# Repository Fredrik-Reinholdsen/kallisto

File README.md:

# Kallisto

A custom split keyboard, with custom electronics and firmware.

The hardware is based around a variant of the _Raspberry Pi Pico_ board, and the _RP2040_ microcontroller.
The keyboard features:

- 42 Kailh 1350 mechanical keyswitches (21 per half), 4 extra buttons and one rotary encoder.
- Fully programmable key-map were any key can be mapped to any key/media function.
- Key-map Layers
- Custom RGB lighting with adjustable brightness
- Onboard flash memory that hold the key-map.

All electronics were designed using KiCad, and all firmware is written in Rust.

## Key Mapping
Any physical key on the keyboard may be mapped to any key, with or without an additional modifier.
Buttons have a few different press modes, similar to the *QMK* firmware, that you can map separatley to different keys.

The different key press types/events are:
- Press
- Held Press
- Double Press

### Held Press
A held press is when a button is pressed and held, for a set ammount of time (0.5s by default).
If a button has a held press mapping is pressed and then released before the held-time window,
then the regular _Press_ mapping while fire upon the release, not the press.
If another button is pressed before the end of the held-time window, then the held press mapping while fire immediatley,
and the other pressed button will fire right after.
If a button with a held press mapping is pressed and held for more than the held-time window, and no other button is pressed in between,
then the held press key mapping will fire.

## Software Design
The right half of the keyboard connected to the host PC acts as the master, and the the left half as the slave.
Compiling the embedded software will generate two separate binaries, one for the master half, and one for the slave.

The slave software is very light-weight and is basically only reading the button matrix, and communicating the current
button states to the master half vi I2C. This means that the slave, once flashed, should rarely need to be re-programmed since the
vast majority of the more complicated application code is running on the master half.

Below is a figure showing the overall architecture of the software that is running on each half of the keyboard.
```mermaid
flowchart RL
    subgraph Master
        direction BT
        BMR[Button Matrix] --> KEGR(Key Event Generator)
        KEGR -->|Key Event| BEG(Button Event Generator)
        BEG -->|Button Event| BEM(Button Event Mapper)
        BEM -->|USB HID Event| USB(USB HID)
    end

    subgraph Slave
        direction BT
        BML[Button Matrix] --> KEGL(Key Event Generator)
    end

    Slave -->|Key Events| Master
```
### Key Event Generator
The `Key Event Generator` reads the current states of all keyboard buttons from the button matrix driver, and generates key press events.
Either key-down or key-up events, based on the current, and the previous button states. Key press events and IDs are constantly
streamed from the slave to the master half via I2C.
These key events from both halves are then queued on the master, along with a unique button ID for which physical button that triggered the event.

### Button Event Generator
The `Button Event Generator` then reads the incoming key press events, and correspoding button IDs from the key-event queue.
This information is then used to generate `Button Events`. The different kinds are:
- Single Press
- Held Press
- Double Press

A held press is triggered if a button is pressed and held for more than 0.3 seconds, and a double press is generated
if a button is pressed twice within 0.3 seconds (these times are tweakable).

The button events along with the ID of which physical button produced the event are then passed `Button Event Mapper`

### Button Event Mapper
The `Button Event Mapper` then maps the incoming button IDs and button event types to a key-press to be sent to the host PC via USB.
For example, single pressing the z-key might map to `z`, but pressing and hold it might map to `Ctrl`. This mapping for each physical button,
and button event type is fully customizable.

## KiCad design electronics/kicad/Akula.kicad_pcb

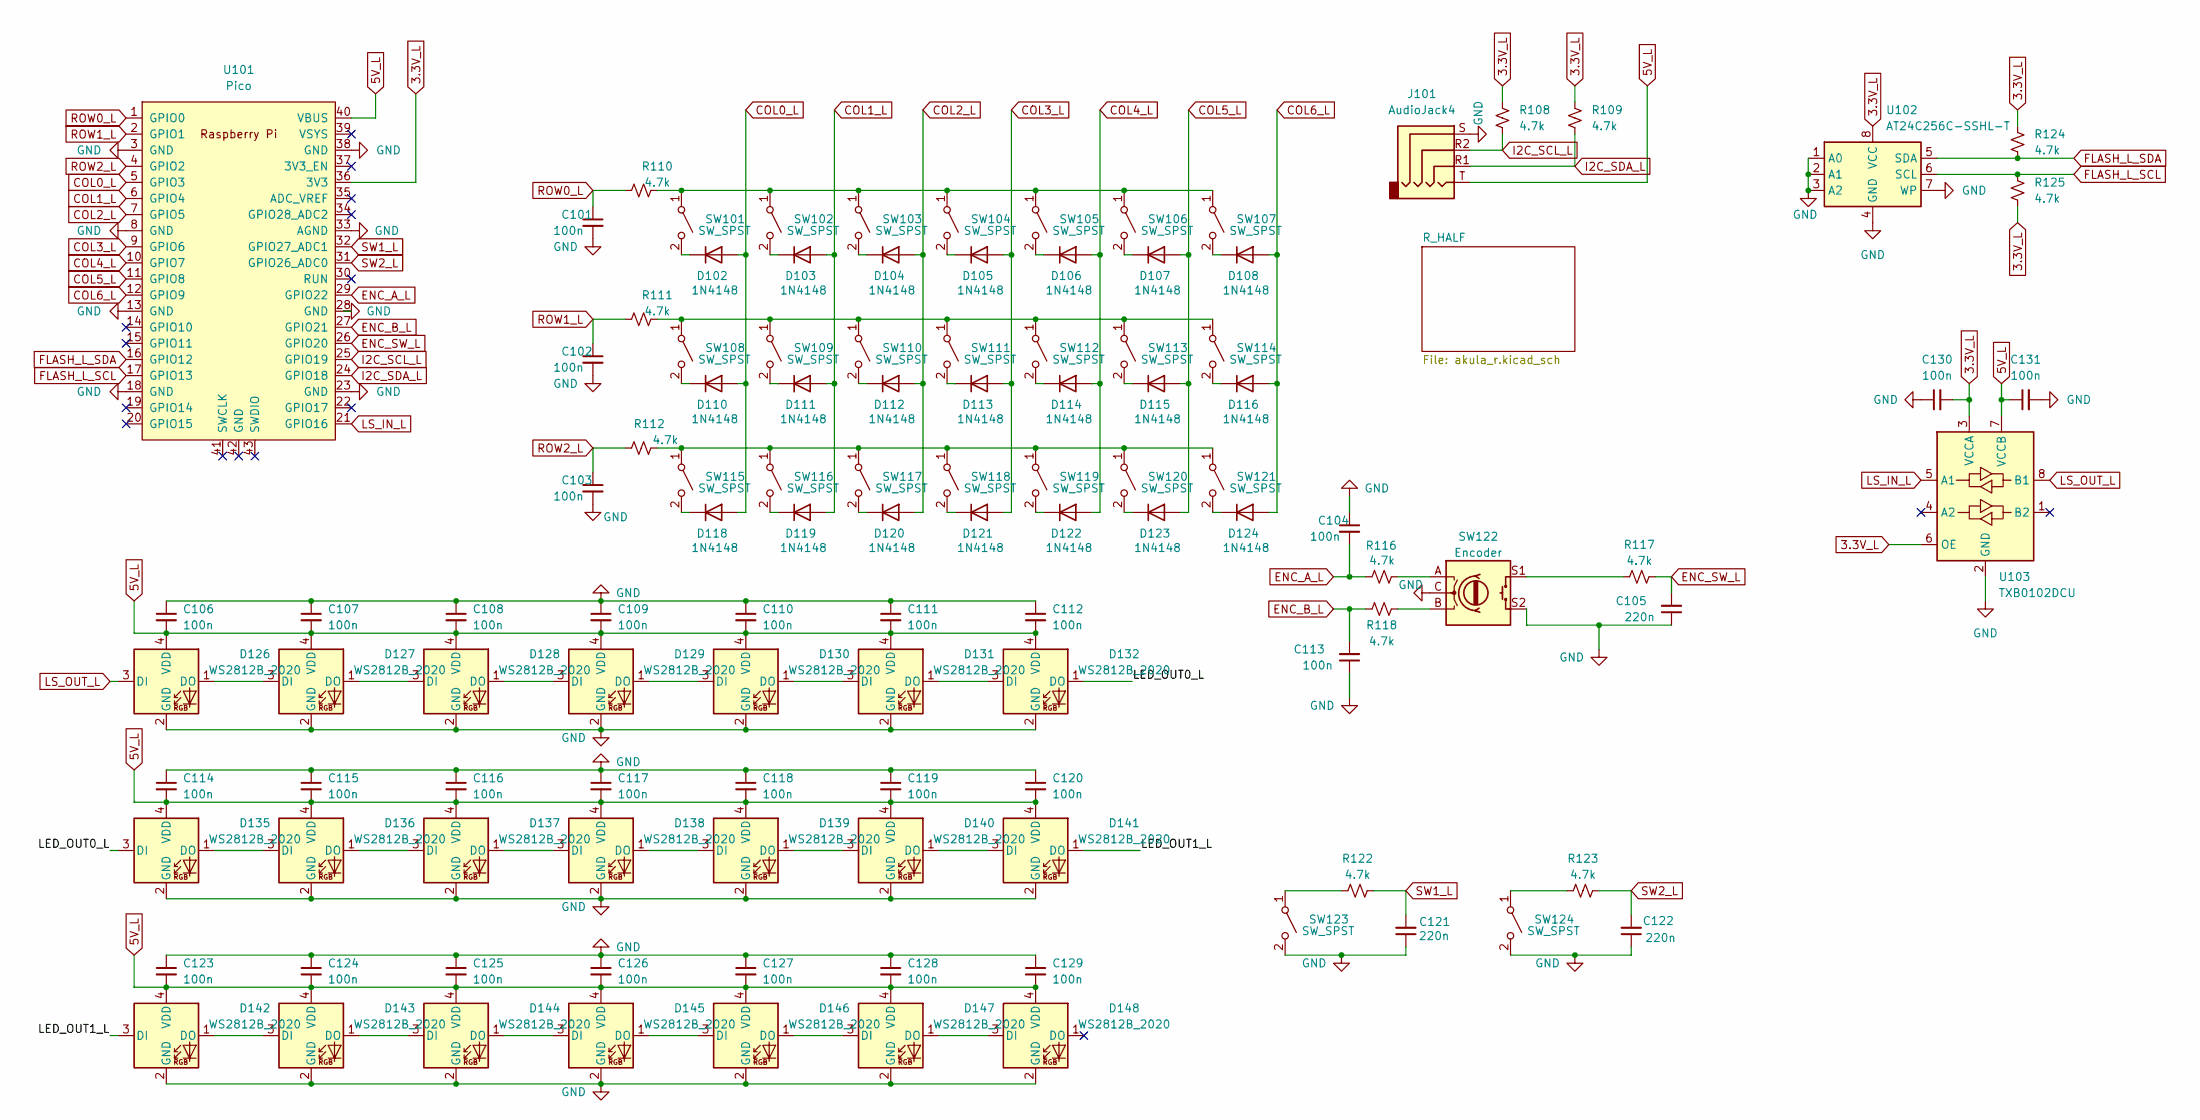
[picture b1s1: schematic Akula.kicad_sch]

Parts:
C101, C102, C103, C104, C106, C107, C108, C109, C110, C111, C112, C113, C114, C115, C116, C117, C118, C119, C120, C123, C124, C125, C126, C127, C128, C129, C130, C131: 100n; C_0402_1005Metric; JLCPCB Part # C1525
C105, C121, C122: 220n; C_0402_1005Metric; JLCPCB Part # C16772
D102, D103, D104, D105, D106, D107, D108, D110, D111, D112, D113, D114, D115, D116, D118, D119, D120, D121, D122, D123, D124: 1N4148; D_SOD-323; JLCPCB Part # C2128
D126, D127, D128, D129, D130, D131, D132, D135, D136, D137, D138, D139, D140, D141, D142, D143, D144, D145, D146, D147, D148: WS2812B_2020; LED_WS2812B-2020_PLCC4_2.0x2.0mm; JLCPCB Part # C965555
J101: AudioJack4; Jack_3.5mm_PJ320D_Horizontal; JLCPCB Part # C431535
R108, R109, R110, R111, R112, R116, R117, R118, R122, R123, R124, R125: 4.7k; R_0402_1005Metric; JLCPCB Part # C25900
SW101, SW102, SW103, SW104, SW105, SW106, SW107, SW108, SW109, SW110, SW111, SW112, SW113, SW114, SW115, SW116, SW117, SW118, SW119, SW120, SW121: SW_SPST; SW_PG1350
SW122: Encoder; RotaryEncoder_Alps_EC11E-Switch_Vertical_H20mm_CircularMoun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; JLCPCB Part # C470753
SW123, SW124: SW_SPST; SW_PUSH-12mm; JLCPCB Part # C93155
U101: Pico; RPi_Pico_SMD_TH
U102: AT24C256C-SSHL-T; SOIC-8_3.9x4.9mm_P1.27mm; JLCPCB Part # C6482
U103: TXB0102DCU; VSSOP-8_2.4x2.1mm_P0.5mm; JLCPCB Part # C2677366

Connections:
3.3V_L: C130.2, R108.2, R109.2, R124.2, R125.2, U101.36 (3V3), U102.8 (VCC), U103.3 (VCCA), U103.6 (OE)
5V_L: C106.2, C107.2, C108.2, C109.2, C110.2, C111.2, C112.2, C114.2, C115.2, C116.2, C117.2, C118.2, C119.2, C120.2, C123.2, C124.2, C125.2, C126.2, C127.2, C128.2, C129.2, C131.1, D126.4 (VDD), D127.4 (VDD), D128.4 (VDD), D129.4 (VDD), D130.4 (VDD), D131.4 (VDD), D132.4 (VDD), D135.4 (VDD), D136.4 (VDD), D137.4 (VDD), D138.4 (VDD), D139.4 (VDD), D140.4 (VDD), D141.4 (VDD), D142.4 (VDD), D143.4 (VDD), D144.4 (VDD), D145.4 (VDD), D146.4 (VDD), D147.4 (VDD), D148.4 (VDD), J101.T, U101.40 (VBUS), U103.7 (VCCB)
/LED_OUT0_L: D132.1 (DO), D135.3 (DI)
/LED_OUT1_L: D141.1 (DO), D142.3 (DI)
COL0_L: D102.2 (A), D110.2 (A), D118.2 (A), U101.5 (GPIO3)
COL1_L: D103.2 (A), D111.2 (A), D119.2 (A), U101.6 (GPIO4)
COL2_L: D104.2 (A), D112.2 (A), D120.2 (A), U101.7 (GPIO5)
COL3_L: D105.2 (A), D113.2 (A), D121.2 (A), U101.9 (GPIO6)
COL4_L: D106.2 (A), D114.2 (A), D122.2 (A), U101.10 (GPIO7)
COL5_L: D107.2 (A), D115.2 (A), D123.2 (A), U101.11 (GPIO8)
COL6_L: D108.2 (A), D116.2 (A), D124.2 (A), U101.12 (GPIO9)
ENC_A_L: C104.2, R116.2, U101.29 (GPIO22)
ENC_B_L: C113.2, R118.2, U101.27 (GPIO21)
ENC_SW_L: C105.2, R117.1, U101.26 (GPIO20)
FLASH_L_SCL: R125.1, U101.17 (GPIO13), U102.6 (SCL)
FLASH_L_SDA: R124.1, U101.16 (GPIO12), U102.5 (SDA)
GND: C101.2, C102.2, C103.2, C104.1, C105.1, C106.1, C107.1, C108.1, C109.1, C110.1, C111.1, C112.1, C113.1, C114.1, C115.1, C116.1, C117.1, C118.1, C119.1, C120.1, C121.1, C122.1, C123.1, C124.1, C125.1, C126.1, C127.1, C128.1, C129.1, C130.1, C131.2, D126.2 (GND), D127.2 (GND), D128.2 (GND), D129.2 (GND), D130.2 (GND), D131.2 (GND), D132.2 (GND), D135.2 (GND), D136.2 (GND), D137.2 (GND), D138.2 (GND), D139.2 (GND), D140.2 (GND), D141.2 (GND), D142.2 (GND), D143.2 (GND), D144.2 (GND), D145.2 (GND), D146.2 (GND), D147.2 (GND), D148.2 (GND), J101.S, SW122.C, SW122.S2, SW123.2 (B), SW124.2 (B), U101.3 (GND), U101.8 (GND), U101.13 (GND), U101.18 (GND), U101.23 (GND), U101.28 (GND), U101.33 (AGND), U101.38 (GND), U102.1 (A0), U102.2 (A1), U102.3 (A2), U102.4 (GND), U102.7 (WP), U103.2 (GND)
I2C_SCL_L: J101.R2, R108.1, U101.25 (GPIO19)
I2C_SDA_L: J101.R1, R109.1, U101.24 (GPIO18)
LS_IN_L: U101.21 (GPIO16), U103.5 (A1)
LS_OUT_L: D126.3 (DI), U103.8 (B1)
unnamed: D102.1 (K), SW101.2 (B)
unnamed: D103.1 (K), SW102.2 (B)
unnamed: D104.1 (K), SW103.2 (B)
unnamed: D105.1 (K), SW104.2 (B)
unnamed: D106.1 (K), SW105.2 (B)
unnamed: D107.1 (K), SW106.2 (B)
unnamed: D108.1 (K), SW107.2 (B)
unnamed: D110.1 (K), SW108.2 (B)
unnamed: D111.1 (K), SW109.2 (B)
unnamed: D112.1 (K), SW110.2 (B)
unnamed: D113.1 (K), SW111.2 (B)
unnamed: D114.1 (K), SW112.2 (B)
unnamed: D115.1 (K), SW113.2 (B)
unnamed: D116.1 (K), SW114.2 (B)
unnamed: D118.1 (K), SW115.2 (B)
unnamed: D119.1 (K), SW116.2 (B)
unnamed: D120.1 (K), SW117.2 (B)
unnamed: D121.1 (K), SW118.2 (B)
unnamed: D122.1 (K), SW119.2 (B)
unnamed: D123.1 (K), SW120.2 (B)
unnamed: D124.1 (K), SW121.2 (B)
unnamed: D126.1 (DO), D127.3 (DI)
unnamed: D127.1 (DO), D128.3 (DI)
unnamed: D128.1 (DO), D129.3 (DI)
unnamed: D129.1 (DO), D130.3 (DI)
unnamed: D130.1 (DO), D131.3 (DI)
unnamed: D131.1 (DO), D132.3 (DI)
unnamed: D135.1 (DO), D136.3 (DI)
unnamed: D136.1 (DO), D137.3 (DI)
unnamed: D137.1 (DO), D138.3 (DI)
unnamed: D138.1 (DO), D139.3 (DI)
unnamed: D139.1 (DO), D140.3 (DI)
unnamed: D140.1 (DO), D141.3 (DI)
unnamed: D142.1 (DO), D143.3 (DI)
unnamed: D143.1 (DO), D144.3 (DI)
unnamed: D144.1 (DO), D145.3 (DI)
unnamed: D145.1 (DO), D146.3 (DI)
unnamed: D146.1 (DO), D147.3 (DI)
unnamed: D147.1 (DO), D148.3 (DI)
unnamed: R116.1, SW122.A
unnamed: R117.2, SW122.S1
unnamed: R118.1, SW122.B
unnamed: R110.1, SW101.1 (A), SW102.1 (A), SW103.1 (A), SW104.1 (A), SW105.1 (A), SW106.1 (A), SW107.1 (A)
unnamed: R111.1, SW108.1 (A), SW109.1 (A), SW110.1 (A), SW111.1 (A), SW112.1 (A), SW113.1 (A), SW114.1 (A)
unnamed: R112.1, SW115.1 (A), SW116.1 (A), SW117.1 (A), SW118.1 (A), SW119.1 (A), SW120.1 (A), SW121.1 (A)
unnamed: R122.2, SW123.1 (A)
unnamed: R123.2, SW124.1 (A)
ROW0_L: C101.1, R110.2, U101.1 (GPIO0)
ROW1_L: C102.1, R111.2, U101.2 (GPIO1)
ROW2_L: C103.1, R112.2, U101.4 (GPIO2)
SW1_L: C121.2, R122.1, U101.32 (GPIO27_ADC1)
SW2_L: C122.2, R123.1, U101.31 (GPIO26_ADC0)

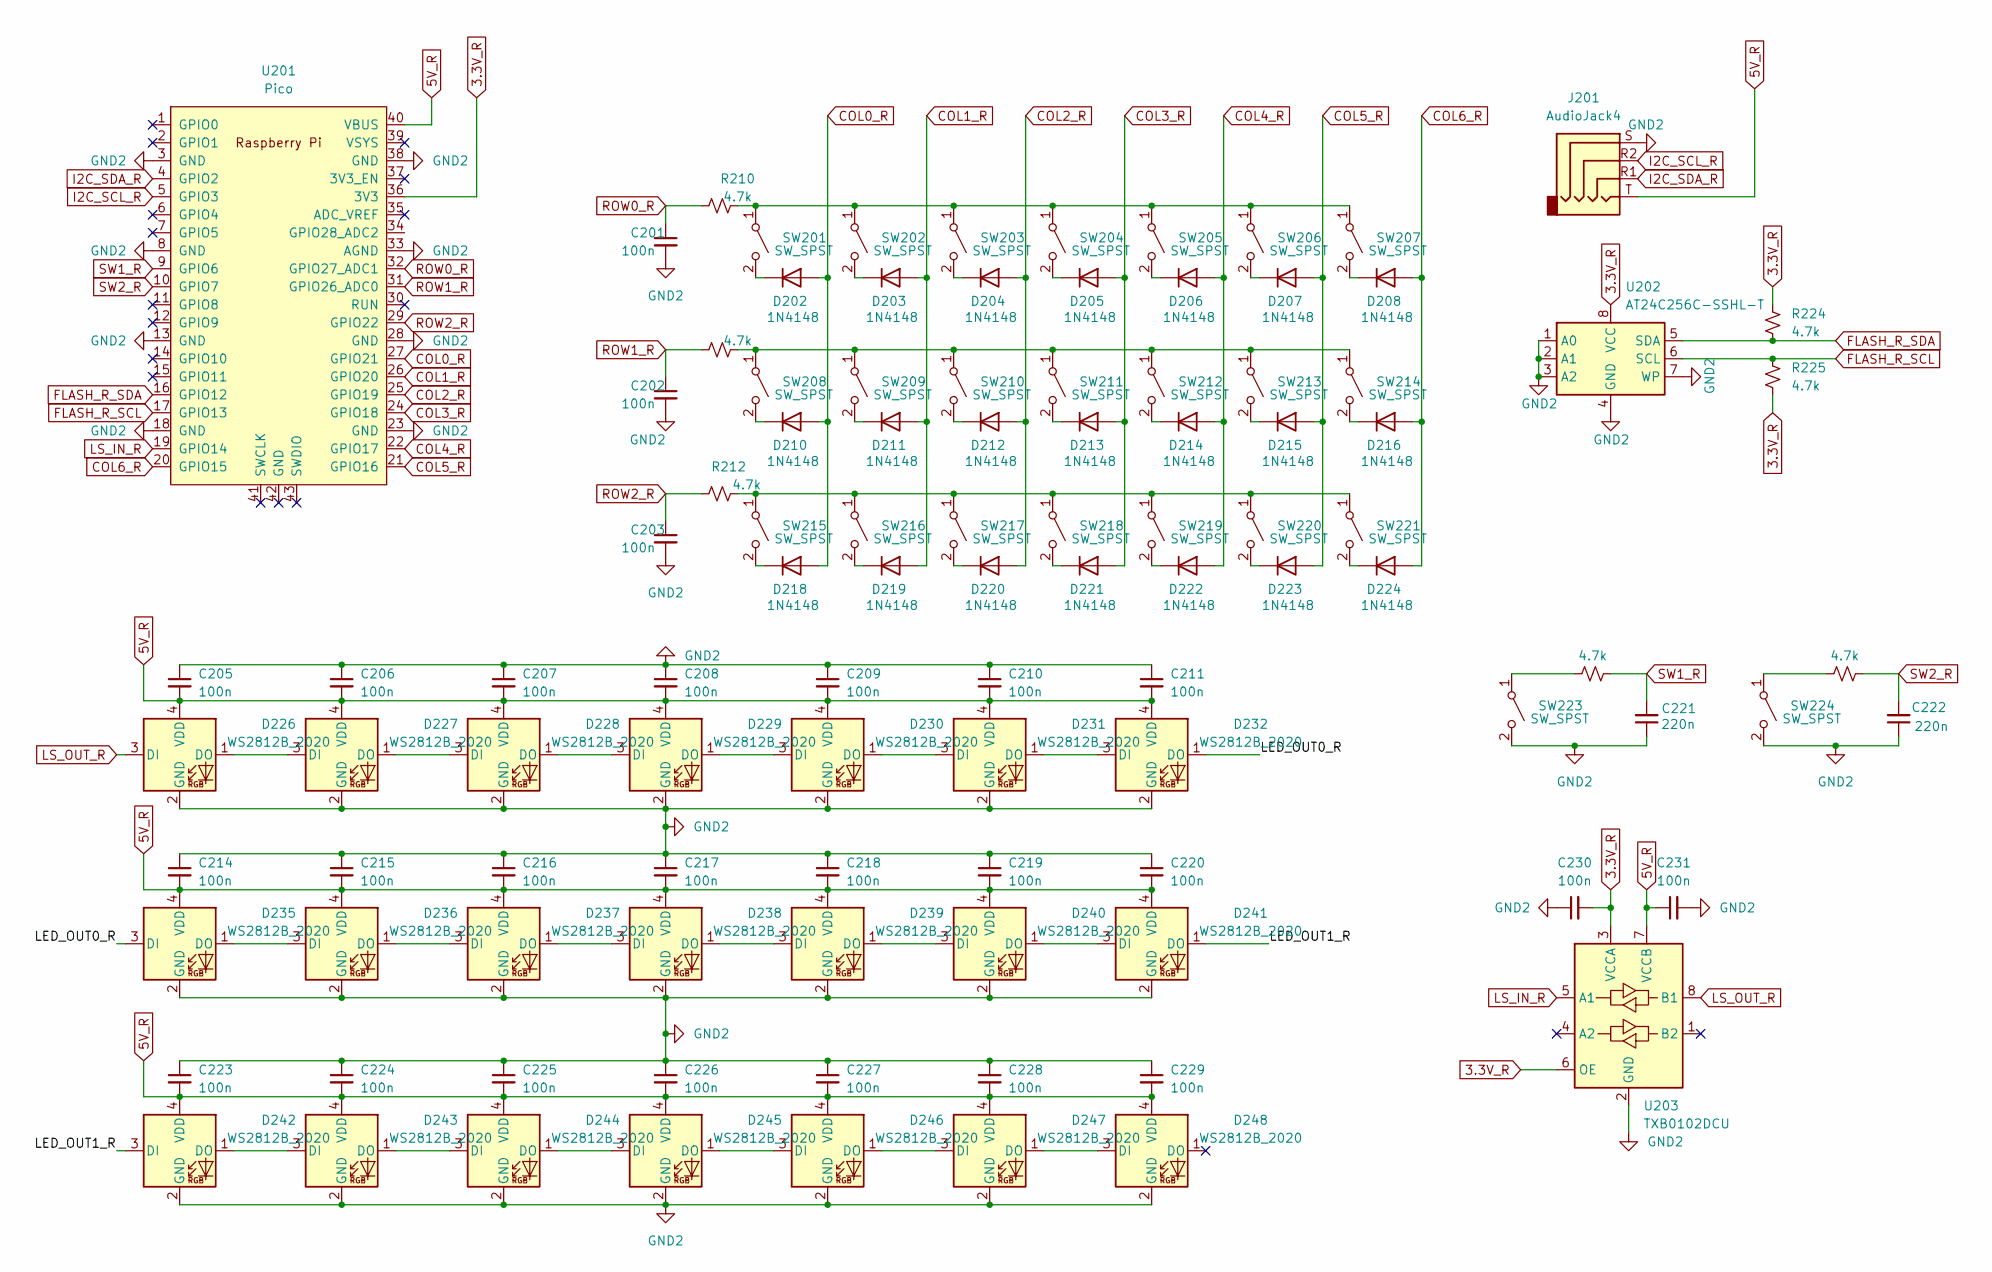
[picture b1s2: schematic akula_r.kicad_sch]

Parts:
C201, C202, C203, C205, C206, C207, C208, C209, C210, C211, C214, C215, C216, C217, C218, C219, C220, C223, C224, C225, C226, C227, C228, C229, C230, C231: 100n; C_0402_1005Metric; JLCPCB Part # C1525
C221, C222: 220n; C_0402_1005Metric; JLCPCB Part # C16772
D202, D203, D204, D205, D206, D207, D208, D210, D211, D212, D213, D214, D215, D216, D218, D219, D220, D221, D222, D223, D224: 1N4148; D_SOD-323; JLCPCB Part # C2128
D226, D227, D228, D229, D230, D231, D232, D235, D236, D237, D238, D239, D240, D241, D242, D243, D244, D245, D246, D247, D248: WS2812B_2020; LED_WS2812B-2020_PLCC4_2.0x2.0mm; JLCPCB Part # C965555
J201: AudioJack4; Jack_3.5mm_PJ320D_Horizontal; JLCPCB Part # C431535
R210, R211, R212, R222, R223, R224, R225: 4.7k; R_0402_1005Metric; JLCPCB Part # C25900
SW201, SW202, SW203, SW204, SW205, SW206, SW207, SW208, SW209, SW210, SW211, SW212, SW213, SW214, SW215, SW216, SW217, SW218, SW219, SW220, SW221: SW_SPST; SW_PG1350
SW223, SW224: SW_SPST; SW_PUSH-12mm; JLCPCB Part # C93155
U201: Pico; RPi_Pico_SMD_TH
U202: AT24C256C-SSHL-T; SOIC-8_3.9x4.9mm_P1.27mm; JLCPCB Part # C6482
U203: TXB0102DCU; VSSOP-8_2.4x2.1mm_P0.5mm; JLCPCB Part # C2677366

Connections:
3.3V_R: C230.2, R224.2, R225.2, U201.36 (3V3), U202.8 (VCC), U203.3 (VCCA), U203.6 (OE)
5V_R: C205.2, C206.2, C207.2, C208.2, C209.2, C210.2, C211.2, C214.2, C215.2, C216.2, C217.2, C218.2, C219.2, C220.2, C223.2, C224.2, C225.2, C226.2, C227.2, C228.2, C229.2, C231.1, D226.4 (VDD), D227.4 (VDD), D228.4 (VDD), D229.4 (VDD), D230.4 (VDD), D231.4 (VDD), D232.4 (VDD), D235.4 (VDD), D236.4 (VDD), D237.4 (VDD), D238.4 (VDD), D239.4 (VDD), D240.4 (VDD), D241.4 (VDD), D242.4 (VDD), D243.4 (VDD), D244.4 (VDD), D245.4 (VDD), D246.4 (VDD), D247.4 (VDD), D248.4 (VDD), J201.T, U201.40 (VBUS), U203.7 (VCCB)
/R_HALF/LED_OUT0_R: D232.1 (DO), D235.3 (DI)
/R_HALF/LED_OUT1_R: D241.1 (DO), D242.3 (DI)
COL0_R: D202.2 (A), D210.2 (A), D218.2 (A), U201.27 (GPIO21)
COL1_R: D203.2 (A), D211.2 (A), D219.2 (A), U201.26 (GPIO20)
COL2_R: D204.2 (A), D212.2 (A), D220.2 (A), U201.25 (GPIO19)
COL3_R: D205.2 (A), D213.2 (A), D221.2 (A), U201.24 (GPIO18)
COL4_R: D206.2 (A), D214.2 (A), D222.2 (A), U201.22 (GPIO17)
COL5_R: D207.2 (A), D215.2 (A), D223.2 (A), U201.21 (GPIO16)
COL6_R: D208.2 (A), D216.2 (A), D224.2 (A), U201.20 (GPIO15)
FLASH_R_SCL: R225.1, U201.17 (GPIO13), U202.6 (SCL)
FLASH_R_SDA: R224.1, U201.16 (GPIO12), U202.5 (SDA)
GND2: C201.2, C202.2, C203.2, C205.1, C206.1, C207.1, C208.1, C209.1, C210.1, C211.1, C214.1, C215.1, C216.1, C217.1, C218.1, C219.1, C220.1, C221.1, C222.1, C223.1, C224.1, C225.1, C226.1, C227.1, C228.1, C229.1, C230.1, C231.2, D226.2 (GND), D227.2 (GND), D228.2 (GND), D229.2 (GND), D230.2 (GND), D231.2 (GND), D232.2 (GND), D235.2 (GND), D236.2 (GND), D237.2 (GND), D238.2 (GND), D239.2 (GND), D240.2 (GND), D241.2 (GND), D242.2 (GND), D243.2 (GND), D244.2 (GND), D245.2 (GND), D246.2 (GND), D247.2 (GND), D248.2 (GND), J201.S, SW223.2 (B), SW224.2 (B), U201.3 (GND), U201.8 (GND), U201.13 (GND), U201.18 (GND), U201.23 (GND), U201.28 (GND), U201.33 (AGND), U201.38 (GND), U202.1 (A0), U202.2 (A1), U202.3 (A2), U202.4 (GND), U202.7 (WP), U203.2 (GND)
I2C_SCL_R: J201.R2, U201.5 (GPIO3)
I2C_SDA_R: J201.R1, U201.4 (GPIO2)
LS_IN_R: U201.19 (GPIO14), U203.5 (A1)
LS_OUT_R: D226.3 (DI), U203.8 (B1)
unnamed: D202.1 (K), SW201.2 (B)
unnamed: D203.1 (K), SW202.2 (B)
unnamed: D204.1 (K), SW203.2 (B)
unnamed: D205.1 (K), SW204.2 (B)
unnamed: D206.1 (K), SW205.2 (B)
unnamed: D207.1 (K), SW206.2 (B)
unnamed: D208.1 (K), SW207.2 (B)
unnamed: D210.1 (K), SW208.2 (B)
unnamed: D211.1 (K), SW209.2 (B)
unnamed: D212.1 (K), SW210.2 (B)
unnamed: D213.1 (K), SW211.2 (B)
unnamed: D214.1 (K), SW212.2 (B)
unnamed: D215.1 (K), SW213.2 (B)
unnamed: D216.1 (K), SW214.2 (B)
unnamed: D218.1 (K), SW215.2 (B)
unnamed: D219.1 (K), SW216.2 (B)
unnamed: D220.1 (K), SW217.2 (B)
unnamed: D221.1 (K), SW218.2 (B)
unnamed: D222.1 (K), SW219.2 (B)
unnamed: D223.1 (K), SW220.2 (B)
unnamed: D224.1 (K), SW221.2 (B)
unnamed: D226.1 (DO), D227.3 (DI)
unnamed: D227.1 (DO), D228.3 (DI)
unnamed: D228.1 (DO), D229.3 (DI)
unnamed: D229.1 (DO), D230.3 (DI)
unnamed: D230.1 (DO), D231.3 (DI)
unnamed: D231.1 (DO), D232.3 (DI)
unnamed: D235.1 (DO), D236.3 (DI)
unnamed: D236.1 (DO), D237.3 (DI)
unnamed: D237.1 (DO), D238.3 (DI)
unnamed: D238.1 (DO), D239.3 (DI)
unnamed: D239.1 (DO), D240.3 (DI)
unnamed: D240.1 (DO), D241.3 (DI)
unnamed: D242.1 (DO), D243.3 (DI)
unnamed: D243.1 (DO), D244.3 (DI)
unnamed: D244.1 (DO), D245.3 (DI)
unnamed: D245.1 (DO), D246.3 (DI)
unnamed: D246.1 (DO), D247.3 (DI)
unnamed: D247.1 (DO), D248.3 (DI)
unnamed: R210.1, SW201.1 (A), SW202.1 (A), SW203.1 (A), SW204.1 (A), SW205.1 (A), SW206.1 (A), SW207.1 (A)
unnamed: R211.1, SW208.1 (A), SW209.1 (A), SW210.1 (A), SW211.1 (A), SW212.1 (A), SW213.1 (A), SW214.1 (A)
unnamed: R212.1, SW215.1 (A), SW216.1 (A), SW217.1 (A), SW218.1 (A), SW219.1 (A), SW220.1 (A), SW221.1 (A)
unnamed: R222.2, SW223.1 (A)
unnamed: R223.2, SW224.1 (A)
ROW0_R: C201.1, R210.2, U201.32 (GPIO27_ADC1)
ROW1_R: C202.1, R211.2, U201.31 (GPIO26_ADC0)
ROW2_R: C203.1, R212.2, U201.29 (GPIO22)
SW1_R: C221.2, R222.1, U201.9 (GPIO6)
SW2_R: C222.2, R223.1, U201.10 (GPIO7)

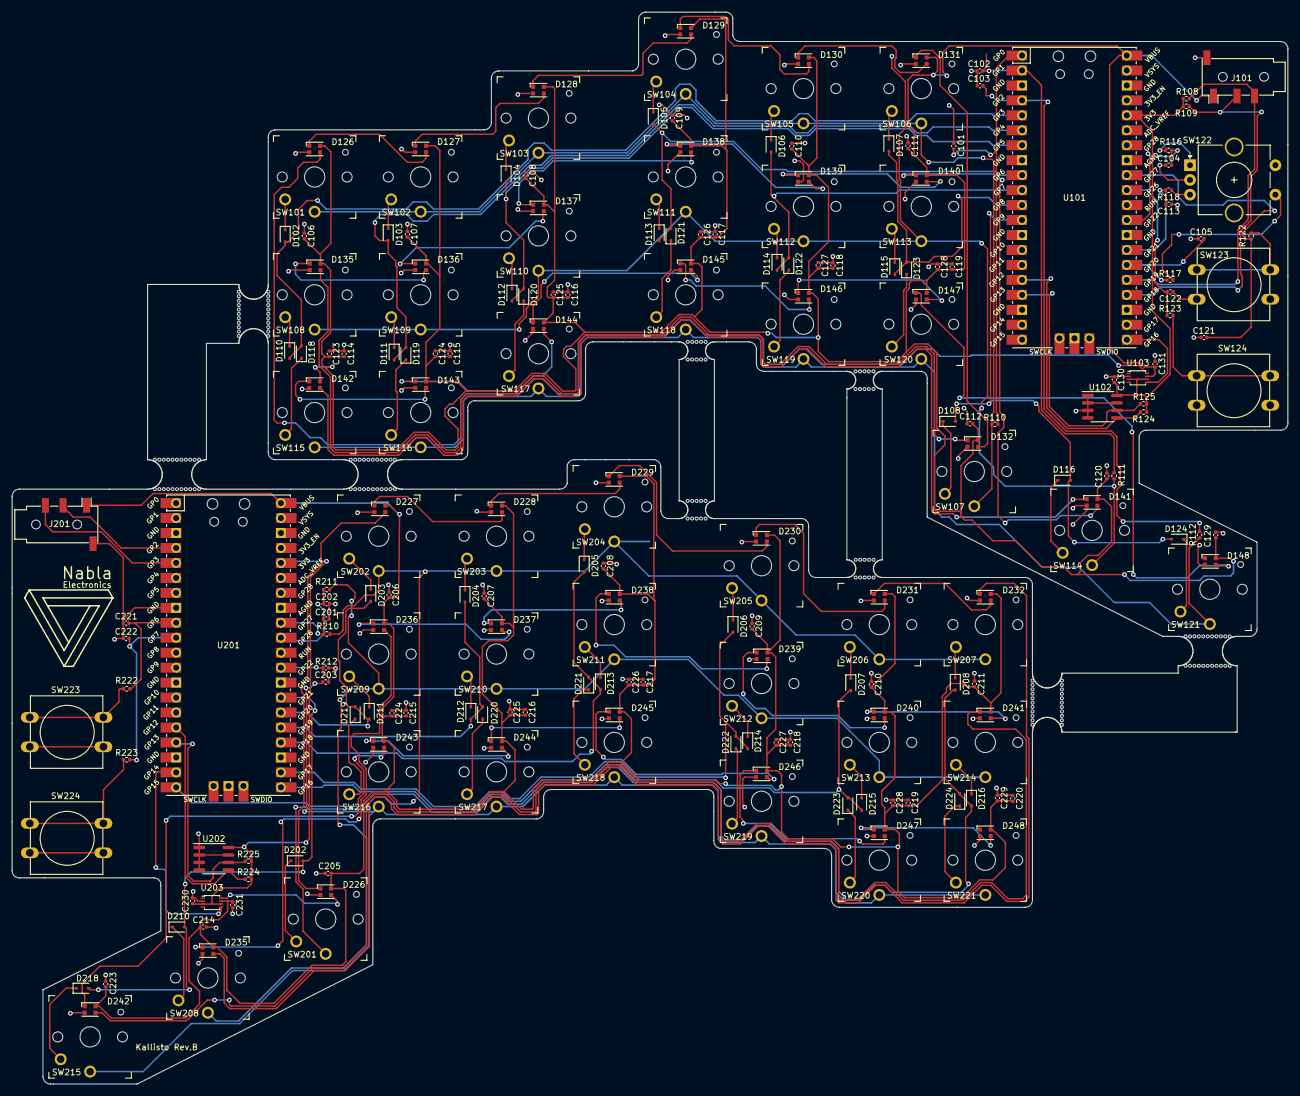
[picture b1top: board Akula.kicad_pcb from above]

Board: 2 copper layers, 216.6 x 182.0 mm, 226 parts (0 on the bottom side), 140 nets.

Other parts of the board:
mouse-bite-3mm-slot, mouse-bite-3mm-slot#2, mouse-bite-3mm-slot#3, mouse-bite-3mm-slot#4: VAL**; mouse-bite-3mm-slot
mouse-bite-5mm-slot, mouse-bite-5mm-slot#2, mouse-bite-5mm-slot#3, mouse-bite-5mm-slot#4, mouse-bite-5mm-slot#5: VAL**; mouse-bite-5mm-slot

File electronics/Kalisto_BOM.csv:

"Comment","Designator","Footprint","LCSC Part #"
"100n","C101,C102,C103,C104,C106,C107,C108,C109,C110,C111,C112,C113,C114,C115,C116,C117,C118,C119,C120,C123,C124,C125,C126,C127,C128,C129,C130,C131,C201,C202,C203,C205,C206,C207,C208,C209,C210,C211,C214,C215,C216,C217,C218,C219,C220,C223,C224,C225,C226,C227,C228,C229,C230,C231","C_0402_1005Metric","C1525"
"220n","C105,C121,C122,C221,C222","C_0402_1005Metric","C16772"
"1N4148","D102,D103,D104,D105,D106,D107,D108,D110,D111,D112,D113,D114,D115,D116,D118,D119,D120,D121,D122,D123,D124,D202,D203,D204,D205,D206,D207,D208,D210,D211,D212,D213,D214,D215,D216,D218,D219,D220,D221,D222,D223,D224","D_SOD-323","C2128"
"WS2812B_2020","D126,D127,D128,D129,D130,D131,D132,D135,D136,D137,D138,D139,D140,D141,D142,D143,D144,D145,D146,D147,D148,D226,D227,D228,D229,D230,D231,D232,D235,D236,D237,D238,D239,D240,D241,D242,D243,D244,D245,D246,D247,D248","LED_WS2812B-2020_PLCC4_2.0x2.0mm","C965555"
"AudioJack4","J101,J201","Jack_3.5mm_PJ320D_Horizontal","C431535"
"4.7k","R108,R109,R110,R111,R112,R116,R117,R118,R122,R123,R124,R125,R210,R211,R212,R222,R223,R224,R225","R_0402_1005Metric","C25900"
"Encoder","SW122","RotaryEncoder_Alps_EC11E-Switch_Vertical_H20mm_CircularMountingHoles","C470753"
"SW_SPST","SW123,SW124,SW223,SW224","SW_PUSH-12mm","C93155"
"AT24C256C-SSHL-T","U102,U202","SOIC-8_3.9x4.9mm_P1.27mm","C6482"
"TXB0102DCU","U103,U203","VSSOP-8_2.4x2.1mm_P0.5mm","C2677366"

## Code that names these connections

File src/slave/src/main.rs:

#![no_std]
#![no_main]

// The macro for our start-up function
use rp_pico::entry;

// Ensure we halt the program on panic (if we don't mention this crate it won't
// be linked)
use panic_halt as _;

// Pull in any important traits
use rp_pico::hal::prelude::*;

// A shorter alias for the Peripheral Access Crate, which provides low-level
// register access
use rp_pico::hal::{self, pac};

// Import the Timer for Ws2812:
use rp_pico::hal::timer::Timer;
use hal::i2c::I2C;
use hal::i2c::peripheral::I2CEvent;

// A shorter alias for the Hardware Abstraction Layer, which provides
// higher-level drivers.
use kallisto_components::keyboard::key_matrix::KeyMatrix;
use embedded_hal::digital::v2::{InputPin, OutputPin};
use embedded_hal::timer::CountDown;
use heapless::{String, spsc::Queue};
use usb_device::class_prelude::*;
use fugit::ExtU32;

use usb_device::{class_prelude::*, prelude::*};
use usbd_serial::SerialPort;
use core::fmt::Write;

use hal::pio::PIOExt;
use smart_leds::{brightness, SmartLedsWrite, RGB8};
use ws2812_pio::Ws2812;

// Currently 3 consecutive LEDs are driven by this example
// to keep the power draw compatible with USB:
const STRIP_LEN: usize = 21;

#[entry]
fn main() -> ! {
    // Grab our singleton objects
    let mut pac = pac::Peripherals::take().unwrap();
    let core = pac::CorePeripherals::take().unwrap();

    // Set up the watchdog driver - needed by the clock setup code
    let mut watchdog = hal::Watchdog::new(pac.WATCHDOG);

    // Configure the clocks
    //
    // The default is to generate a 125 MHz system clock
    let clocks = hal::clocks::init_clocks_and_plls(
        rp_pico::XOSC_CRYSTAL_FREQ,
        pac.XOSC,
        pac.CLOCKS,
        pac.PLL_SYS,
        pac.PLL_USB,
        &mut pac.RESETS,
        &mut watchdog,
    )
    .ok()
    .unwrap();

    // The single-cycle I/O block controls our GPIO pins
    let sio = hal::Sio::new(pac.SIO);

    // Set the pins up according to their function on this particular board
    let pins = rp_pico::Pins::new(
        pac.IO_BANK0,
        pac.PADS_BANK0,
        sio.gpio_bank0,
        &mut pac.RESETS,
    );


    let mut timer = Timer::new(pac.TIMER, &mut pac.RESETS);

    let mut delay = cortex_m::delay::Delay::new(core.SYST, clocks.system_clock.freq().to_Hz());

    // Set up smart leds
    let sin = hal::rom_data::float_funcs::fsin::ptr();

    let (mut pio, sm0, _, _, _) = pac.PIO0.split(&mut pac.RESETS);

    // Instanciate a Ws2812 LED strip:
    let mut ws = Ws2812::new(
        // Use pin 6 on the Raspberry Pi Pico (which is GPIO4 of the rp2040 chip)
        // for the LED data output:
        pins.gpio16.into_mode(),
        &mut pio,
        sm0,
        clocks.peripheral_clock.freq(),
        timer.count_down(),
    );

    // Set up i2c
    let sda_pin = pins.gpio18.into_mode::<hal::gpio::FunctionI2C>();
    let scl_pin = pins.gpio19.into_mode::<hal::gpio::FunctionI2C>();

    let mut i2c = I2C::new_peripheral_event_iterator(
        pac.I2C1,
        sda_pin,
        scl_pin,
        &mut pac.RESETS,
        0x33,
    );
    
    // Set up all pins
    let mut row_pin_0 = pins.gpio0.into_push_pull_output();
    let mut row_pin_1 = pins.gpio1.into_push_pull_output();
    let mut row_pin_2 = pins.gpio2.into_push_pull_output();

    // Setting the output slew rate to fast is absolutley 
    // needed in order to prevent row cross-talk
    row_pin_0.set_slew_rate(hal::gpio::OutputSlewRate::Fast);
    row_pin_1.set_slew_rate(hal::gpio::OutputSlewRate::Fast);
    row_pin_2.set_slew_rate(hal::gpio::OutputSlewRate::Fast);

    // Set up our pins for the key matrix
    let mut row_pins: &mut [&mut dyn OutputPin<Error = core::convert::Infallible>] = &mut [
        &mut row_pin_0,
        &mut row_pin_1,
        &mut row_pin_2,
    ];

    let col_pins: &[&dyn InputPin<Error = core::convert::Infallible>] = &[
        &pins.gpio3.into_pull_up_input(),
        &pins.gpio4.into_pull_up_input(),
        &pins.gpio5.into_pull_up_input(),
        &pins.gpio6.into_pull_up_input(),
        &pins.gpio7.into_pull_up_input(),
        &pins.gpio8.into_pull_up_input(),
        &pins.gpio9.into_pull_up_input(),
    ];

    let mut led_pin = pins.led.into_push_pull_output();
    let mut key_matrix = KeyMatrix::new(&timer);


    led_pin.set_high().unwrap();
    delay.delay_ms(500);
    led_pin.set_low().unwrap();

    let mut leds: [RGB8; STRIP_LEN] = [(0, 0, 0).into(); STRIP_LEN];
    let mut t = 0.0;
    let strip_brightness = 64u8; // Limit brightness to 64/256

    // Slow down timer by this factor (0.1 will result in 10 seconds):
    let animation_speed = 0.1;


    let mut keyboard_timer = timer.count_down();
    let mut led_timer = timer.count_down();

    led_timer.start(17.millis());
    keyboard_timer.start(1.millis());

    let mut key_states: u32 = 0;

    loop {

        if keyboard_timer.wait().is_ok() {
            key_states = key_matrix.poll_row_states(&mut row_pins, &col_pins);
        }

        if led_timer.wait().is_ok() {
            for (i, led) in leds.iter_mut().enumerate() {
                // An offset to give 3 consecutive LEDs a different color:
                let hue_offs = match i % 3 {
                    1 => 0.25,
                    2 => 0.5,
                    _ => 0.0,
                };

                let sin_11 = sin((t + hue_offs) * 2.0 * core::f32::consts::PI);
                // Bring -1..1 sine range to 0..1 range:
                let sin_01 = (sin_11 + 1.0) * 0.5;

                let hue = 360.0 * sin_01;
                let sat = 1.0;
                let val = 1.0;

                let rgb = hsv2rgb_u8(hue, sat, val);
                *led = rgb.into();
            }

            ws.write(brightness(leds.iter().copied(), strip_brightness))
                .unwrap();

            t += (16.0 / 1000.0) * animation_speed;
            while t > 1.0 {
                t -= 1.0;
            }
        }

        let event = i2c.next();
        if event.is_none() {
            continue;
        }

        match event.unwrap() {
            I2CEvent::TransferRead => {
                let _ = i2c.write(&key_states.to_be_bytes());
            }
            _ => continue,
        }
    }
}

pub fn hsv2rgb(hue: f32, sat: f32, val: f32) -> (f32, f32, f32) {
    let c = val * sat;
    let v = (hue / 60.0) % 2.0 - 1.0;
    let v = if v < 0.0 { -v } else { v };
    let x = c * (1.0 - v);
    let m = val - c;
    let (r, g, b) = if hue < 60.0 {
        (c, x, 0.0)
    } else if hue < 120.0 {
        (x, c, 0.0)
    } else if hue < 180.0 {
        (0.0, c, x)
    } else if hue < 240.0 {
        (0.0, x, c)
    } else if hue < 300.0 {
        (x, 0.0, c)
    } else {
        (c, 0.0, x)
    };
    (r + m, g + m, b + m)
}

pub fn hsv2rgb_u8(h: f32, s: f32, v: f32) -> (u8, u8, u8) {
    let r = hsv2rgb(h, s, v);

    (
        (r.0 * 255.0) as u8,
        (r.1 * 255.0) as u8,
        (r.2 * 255.0) as u8,
    )
}

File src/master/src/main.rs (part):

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
    // Instanciate a Ws2812 LED strip:
    let mut ws = Ws2812::new(
        // Use pin 6 on the Raspberry Pi Pico (which is GPIO4 of the rp2040 chip)
        // for the LED data output:
        pins.gpio14.into_mode(),
        &mut pio,
        sm0,
        clocks.peripheral_clock.freq(),
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    );

    // Set up i2c
    let sda_pin = pins.gpio2.into_mode::<hal::gpio::FunctionI2C>();
    let scl_pin = pins.gpio3.into_mode::<hal::gpio::FunctionI2C>();

    let mut i2c = I2C::new_controller(
        pac.I2C1,
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    // Set up all pins
    let mut row_pin_0 = pins.gpio27.into_push_pull_output();
    let mut row_pin_1 = pins.gpio26.into_push_pull_output();
    let mut row_pin_2 = pins.gpio22.into_push_pull_output();

    // Setting the output slew rate to fast is absolutley 
    // needed in order to prevent row cross-talk
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    ];

    let col_pins: &[&dyn InputPin<Error = core::convert::Infallible>] = &[
        &pins.gpio21.into_pull_up_input(),
        &pins.gpio20.into_pull_up_input(),
        &pins.gpio19.into_pull_up_input(),
        &pins.gpio18.into_pull_up_input(),
        &pins.gpio17.into_pull_up_input(),
        &pins.gpio16.into_pull_up_input(),
        &pins.gpio15.into_pull_up_input(),
    ];

    let mut led_pin = pins.led.into_push_pull_output();
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
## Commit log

2023-08-04 Proper implementation of held press functionality, and one change to the default key map.
2023-08-05 Refactor of main layered keyboard code, and modification of debounce constants
2023-08-13 Edit of some default key mappings
2024-08-11 Added additional images, and PDF of Rev B. schematic, and slight formatting change to key map.
